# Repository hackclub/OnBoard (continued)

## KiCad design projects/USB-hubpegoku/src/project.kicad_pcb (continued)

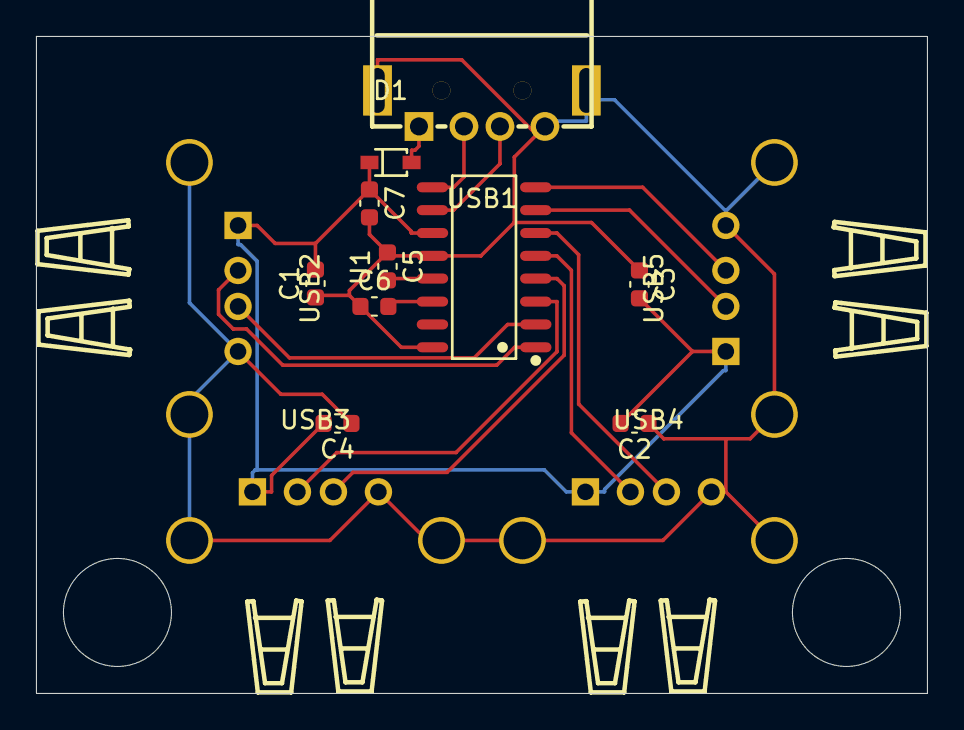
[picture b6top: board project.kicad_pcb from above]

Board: 2 copper layers, 49.5 x 36.5 mm, 14 parts (0 on the bottom side), 15 nets.

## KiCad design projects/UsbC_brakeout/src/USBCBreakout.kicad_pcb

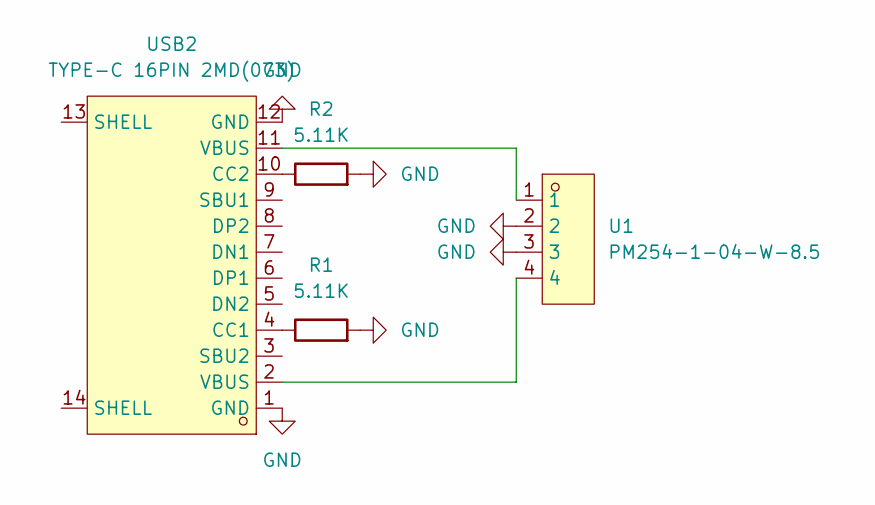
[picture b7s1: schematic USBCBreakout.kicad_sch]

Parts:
R1, R2: 5.11K; R_0603_1608Metric; LCSC C112314
U1: PM254-1-04-W-8.5; HDR-TH_4P-P2.54-H-F-W10.0-N; LCSC Part C2897386
USB2: TYPE-C 16PIN 2MD(073); USB-C-SMD_TYPE-C-6PIN-2MD-073; LCSC Part C2765186

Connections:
GND: R1.2, R2.2, U1.2, U1.3, USB2.1 (GND), USB2.12 (GND)
unnamed: U1.1, USB2.11 (VBUS)
unnamed: U1.4, USB2.2 (VBUS)
unnamed: R1.1, USB2.4 (CC1)
unnamed: R2.1, USB2.10 (CC2)

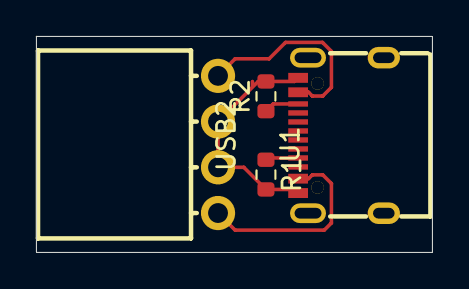
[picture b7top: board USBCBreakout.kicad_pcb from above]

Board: 2 copper layers, 22.0 x 12.0 mm, 4 parts (0 on the bottom side), 5 nets.
